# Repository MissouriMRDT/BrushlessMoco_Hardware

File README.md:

# Brushless Motor Controller R&D
The brushless moco is an electrical board that will simplify the electrical system within the brushless arm. This doesn't only include the brushless arm but also everything else that will use a significantly large brushless motors. This project provides future use cases for both **drivetrain** and **brushless arm** going forth.

[Main Project Document](https://mailmissouri.sharepoint.com/:w:/r/sites/SDELC-MarsRoverDesignTeam-Ogrp/_layouts/15/Doc.aspx?sourcedoc=%7BEC210861-7018-4F6B-87D7-A1866F1C1E35%7D&file=Brushless%20Motor%20Controller.docx&action=default&mobileredirect=true)

[Discord Forum](https://discord.com/channels/988649090306961418/1396668404471042090)

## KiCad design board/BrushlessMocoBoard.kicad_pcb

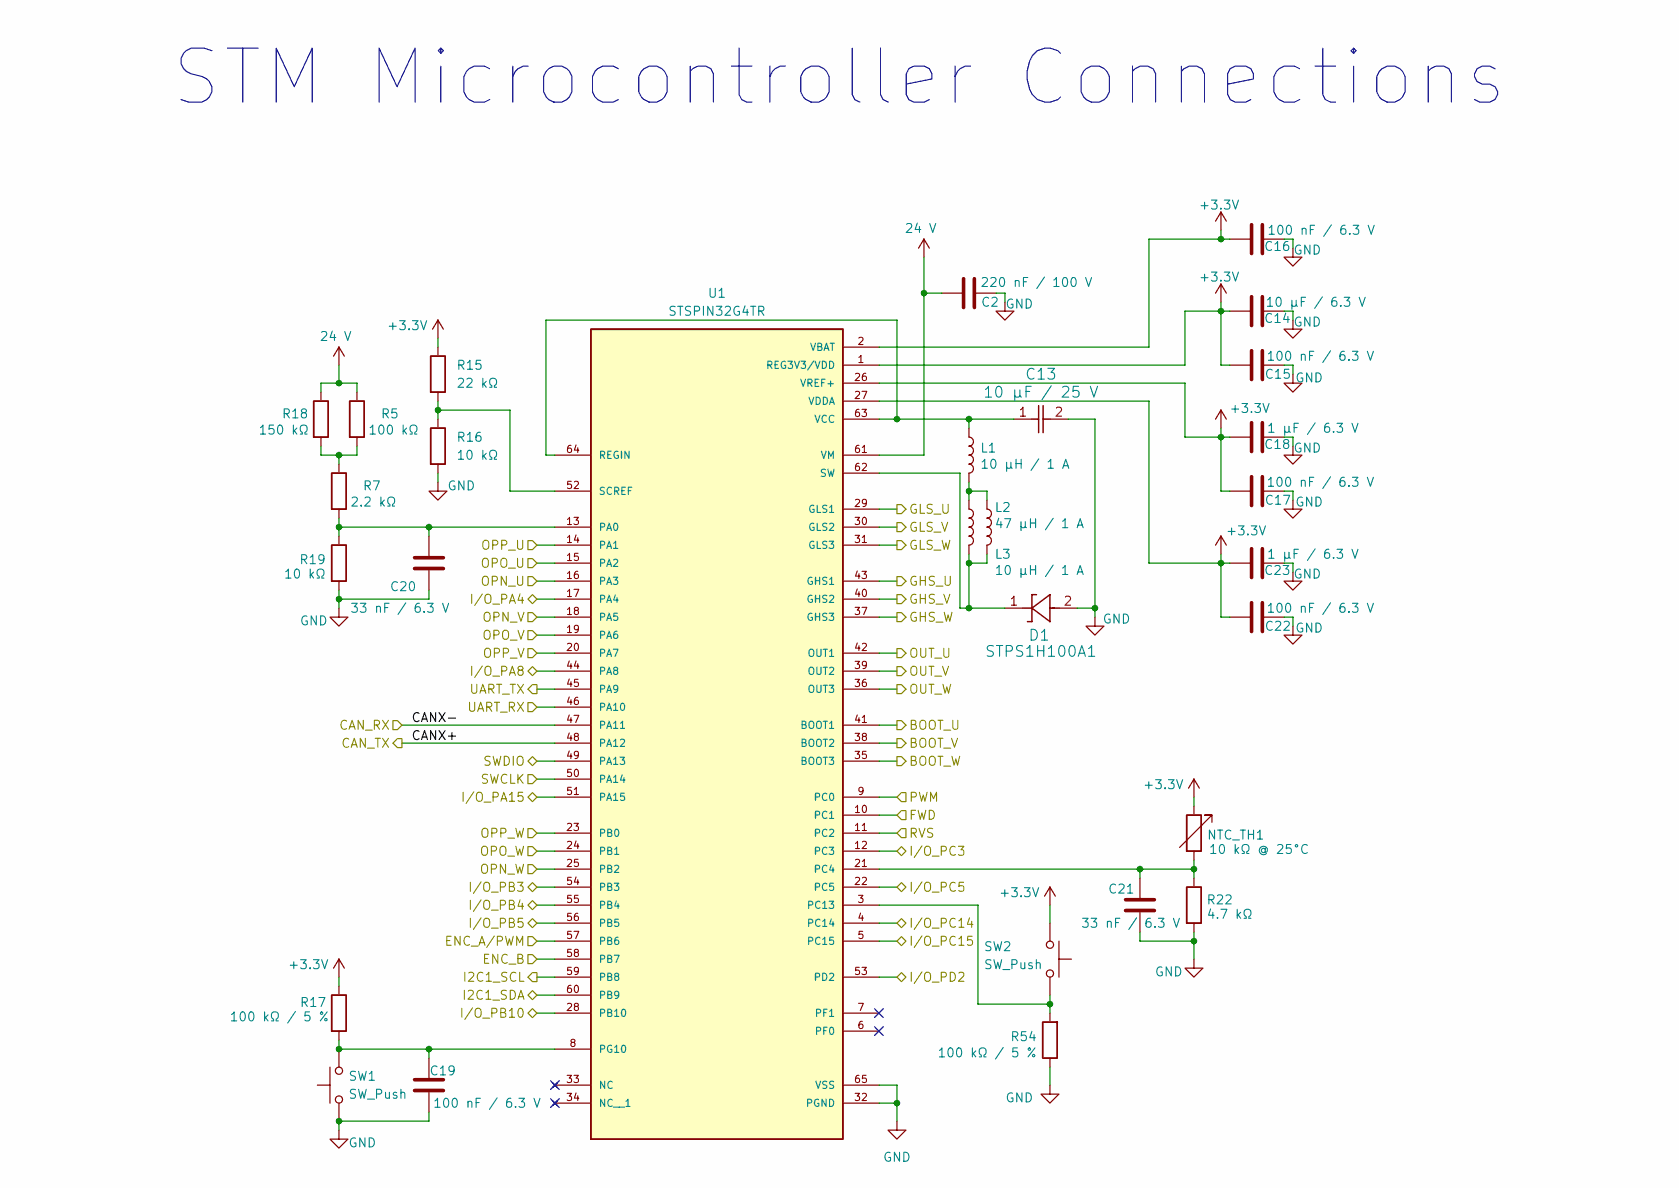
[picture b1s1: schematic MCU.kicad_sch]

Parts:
C2: 220 nF / 100 V; C_0603_1608Metric_Pad1.08x0.95mm_HandSolder
C13: 10 µF / 25 V; CAP_PAN_4X7_PAN
C14: 10 μF / 6.3 V; C_0603_1608Metric_Pad1.08x0.95mm_HandSolder
C15, C16, C17, C19, C22: 100 nF / 6.3 V; C_0603_1608Metric_Pad1.08x0.95mm_HandSolder
C18, C23: 1 μF / 6.3 V; C_0603_1608Metric_Pad1.08x0.95mm_HandSolder
C20, C21: 33 nF / 6.3 V; C_0603_1608Metric_Pad1.08x0.95mm_HandSolder
L1, L3: 10 μH / 1 A; L_1008_2520Metric_Pad1.43x2.20mm_HandSolder
L2: 47 μH / 1 A; IND_VLS5045EX-470M
NTC_TH1: 10 kΩ @ 25°C; R_0603_1608Metric_Pad0.98x0.95mm_HandSolder
R5: 100 kΩ; R_0603_1608Metric_Pad0.98x0.95mm_HandSolder
R7: 2.2 kΩ; R_0603_1608Metric_Pad0.98x0.95mm_HandSolder
R15: 22 kΩ; R_0603_1608Metric_Pad0.98x0.95mm_HandSolder
R16, R19: 10 kΩ; R_0603_1608Metric_Pad0.98x0.95mm_HandSolder
R17, R54: 100 kΩ / 5 %; R_0603_1608Metric_Pad0.98x0.95mm_HandSolder
R18: 150 kΩ; R_0603_1608Metric_Pad0.98x0.95mm_HandSolder
R22: 4.7 kΩ; R_0603_1608Metric_Pad0.98x0.95mm_HandSolder
STPS1H100A1: D1; SMA_STM
SW1, SW2: SW_Push; SW_SPST_TL3305A
U1: STSPIN32G4TR; QFN50P900X900X100-65N; PARTREV 2

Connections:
24 V: C2.1, R5.1, R18.1, U1.61 (VM); also elsewhere on the board
+3.3V: C14.1, C15.1, C16.1, C17.1, C18.1, C22.1, C23.1, NTC_TH1.1, R15.1, R17.1, SW2.1, U1.1 (REG3V3/VDD), U1.2 (VBAT), U1.26 (VREF+), U1.27 (VDDA); also elsewhere on the board
/Half-Bridges & Current Sensing/BOOT_U: U1.41 (BOOT1); also elsewhere on the board
/Half-Bridges & Current Sensing/BOOT_V: U1.38 (BOOT2); also elsewhere on the board
/Half-Bridges & Current Sensing/BOOT_W: U1.35 (BOOT3); also elsewhere on the board
/Half-Bridges & Current Sensing/GHS_U: U1.43 (GHS1); also elsewhere on the board
/Half-Bridges & Current Sensing/GHS_V: U1.40 (GHS2); also elsewhere on the board
/Half-Bridges & Current Sensing/GHS_W: U1.37 (GHS3); also elsewhere on the board
/Half-Bridges & Current Sensing/GLS_U: U1.29 (GLS1); also elsewhere on the board
/Half-Bridges & Current Sensing/GLS_V: U1.30 (GLS2); also elsewhere on the board
/Half-Bridges & Current Sensing/GLS_W: U1.31 (GLS3); also elsewhere on the board
/Half-Bridges & Current Sensing/OPN_U: U1.16 (PA3); also elsewhere on the board
/Half-Bridges & Current Sensing/OPN_V: U1.18 (PA5); also elsewhere on the board
/Half-Bridges & Current Sensing/OPN_W: U1.25 (PB2); also elsewhere on the board
/Half-Bridges & Current Sensing/OPO_U: U1.15 (PA2); also elsewhere on the board
/Half-Bridges & Current Sensing/OPO_V: U1.19 (PA6); also elsewhere on the board
/Half-Bridges & Current Sensing/OPO_W: U1.24 (PB1); also elsewhere on the board
/Half-Bridges & Current Sensing/OPP_U: U1.14 (PA1); also elsewhere on the board
/Half-Bridges & Current Sensing/OPP_V: U1.20 (PA7); also elsewhere on the board
/Half-Bridges & Current Sensing/OPP_W: U1.23 (PB0); also elsewhere on the board
/Half-Bridges & Current Sensing/OUT_U: U1.42 (OUT1); also elsewhere on the board
/Half-Bridges & Current Sensing/OUT_V: U1.39 (OUT2); also elsewhere on the board
/Half-Bridges & Current Sensing/OUT_W: U1.36 (OUT3); also elsewhere on the board
/Interfaces/ENC_A/PWM: U1.57 (PB6); also elsewhere on the board
/Interfaces/ENC_B: U1.58 (PB7); also elsewhere on the board
/Interfaces/FWD: U1.10 (PC1); also elsewhere on the board
/Interfaces/I2C1_SCL: U1.59 (PB8); also elsewhere on the board
/Interfaces/I2C1_SDA: U1.60 (PB9); also elsewhere on the board
/Interfaces/I/O_PA4: U1.17 (PA4); also elsewhere on the board
/Interfaces/I/O_PA8: U1.44 (PA8); also elsewhere on the board
/Interfaces/I/O_PA15: U1.51 (PA15); also elsewhere on the board
/Interfaces/I/O_PB3: U1.54 (PB3); also elsewhere on the board
/Interfaces/I/O_PB4: U1.55 (PB4); also elsewhere on the board
/Interfaces/I/O_PB5: U1.56 (PB5); also elsewhere on the board
/Interfaces/I/O_PB10: U1.28 (PB10); also elsewhere on the board
/Interfaces/I/O_PC3: U1.12 (PC3); also elsewhere on the board
/Interfaces/I/O_PC5: U1.22 (PC5); also elsewhere on the board
/Interfaces/I/O_PC14: U1.4 (PC14); also elsewhere on the board
/Interfaces/I/O_PC15: U1.5 (PC15); also elsewhere on the board
/Interfaces/I/O_PD2: U1.53 (PD2); also elsewhere on the board
/Interfaces/PWM: U1.9 (PC0); also elsewhere on the board
/Interfaces/RVS: U1.11 (PC2); also elsewhere on the board
/Interfaces/SWCLK: U1.50 (PA14); also elsewhere on the board
/Interfaces/SWDIO: U1.49 (PA13); also elsewhere on the board
/Interfaces/UART_RX: U1.46 (PA10); also elsewhere on the board
/Interfaces/UART_TX: U1.45 (PA9); also elsewhere on the board
/MCU/CANX+: U1.48 (PA12); also elsewhere on the board
/MCU/CANX-: U1.47 (PA11); also elsewhere on the board
GND: C2.2, C13.2, C14.2, C15.2, C16.2, C17.2, C18.2, C19.2, C20.2, C21.2, C22.2, C23.2, R16.2, R19.2, R22.2, R54.1, STPS1H100A1.2, SW1.1, U1.32 (PGND), U1.65 (VSS); also elsewhere on the board
unnamed: L1.2, L2.1, L3.1
unnamed: R5.2, R7.1, R18.2
unnamed: C20.1, R7.2, R19.1, U1.13 (PA0)
unnamed: C21.1, NTC_TH1.2, R22.1, U1.21 (PC4)
unnamed: R54.2, SW2.2, U1.3 (PC13)
unnamed: C19.1, R17.2, SW1.2, U1.8 (PG10)
unnamed: C13.1, L1.1, U1.63 (VCC), U1.64 (REGIN)
unnamed: R15.2, R16.1, U1.52 (SCREF)
unnamed: L2.2, L3.2, STPS1H100A1.1, U1.62 (SW)

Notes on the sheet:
STM Microcontroller Connections

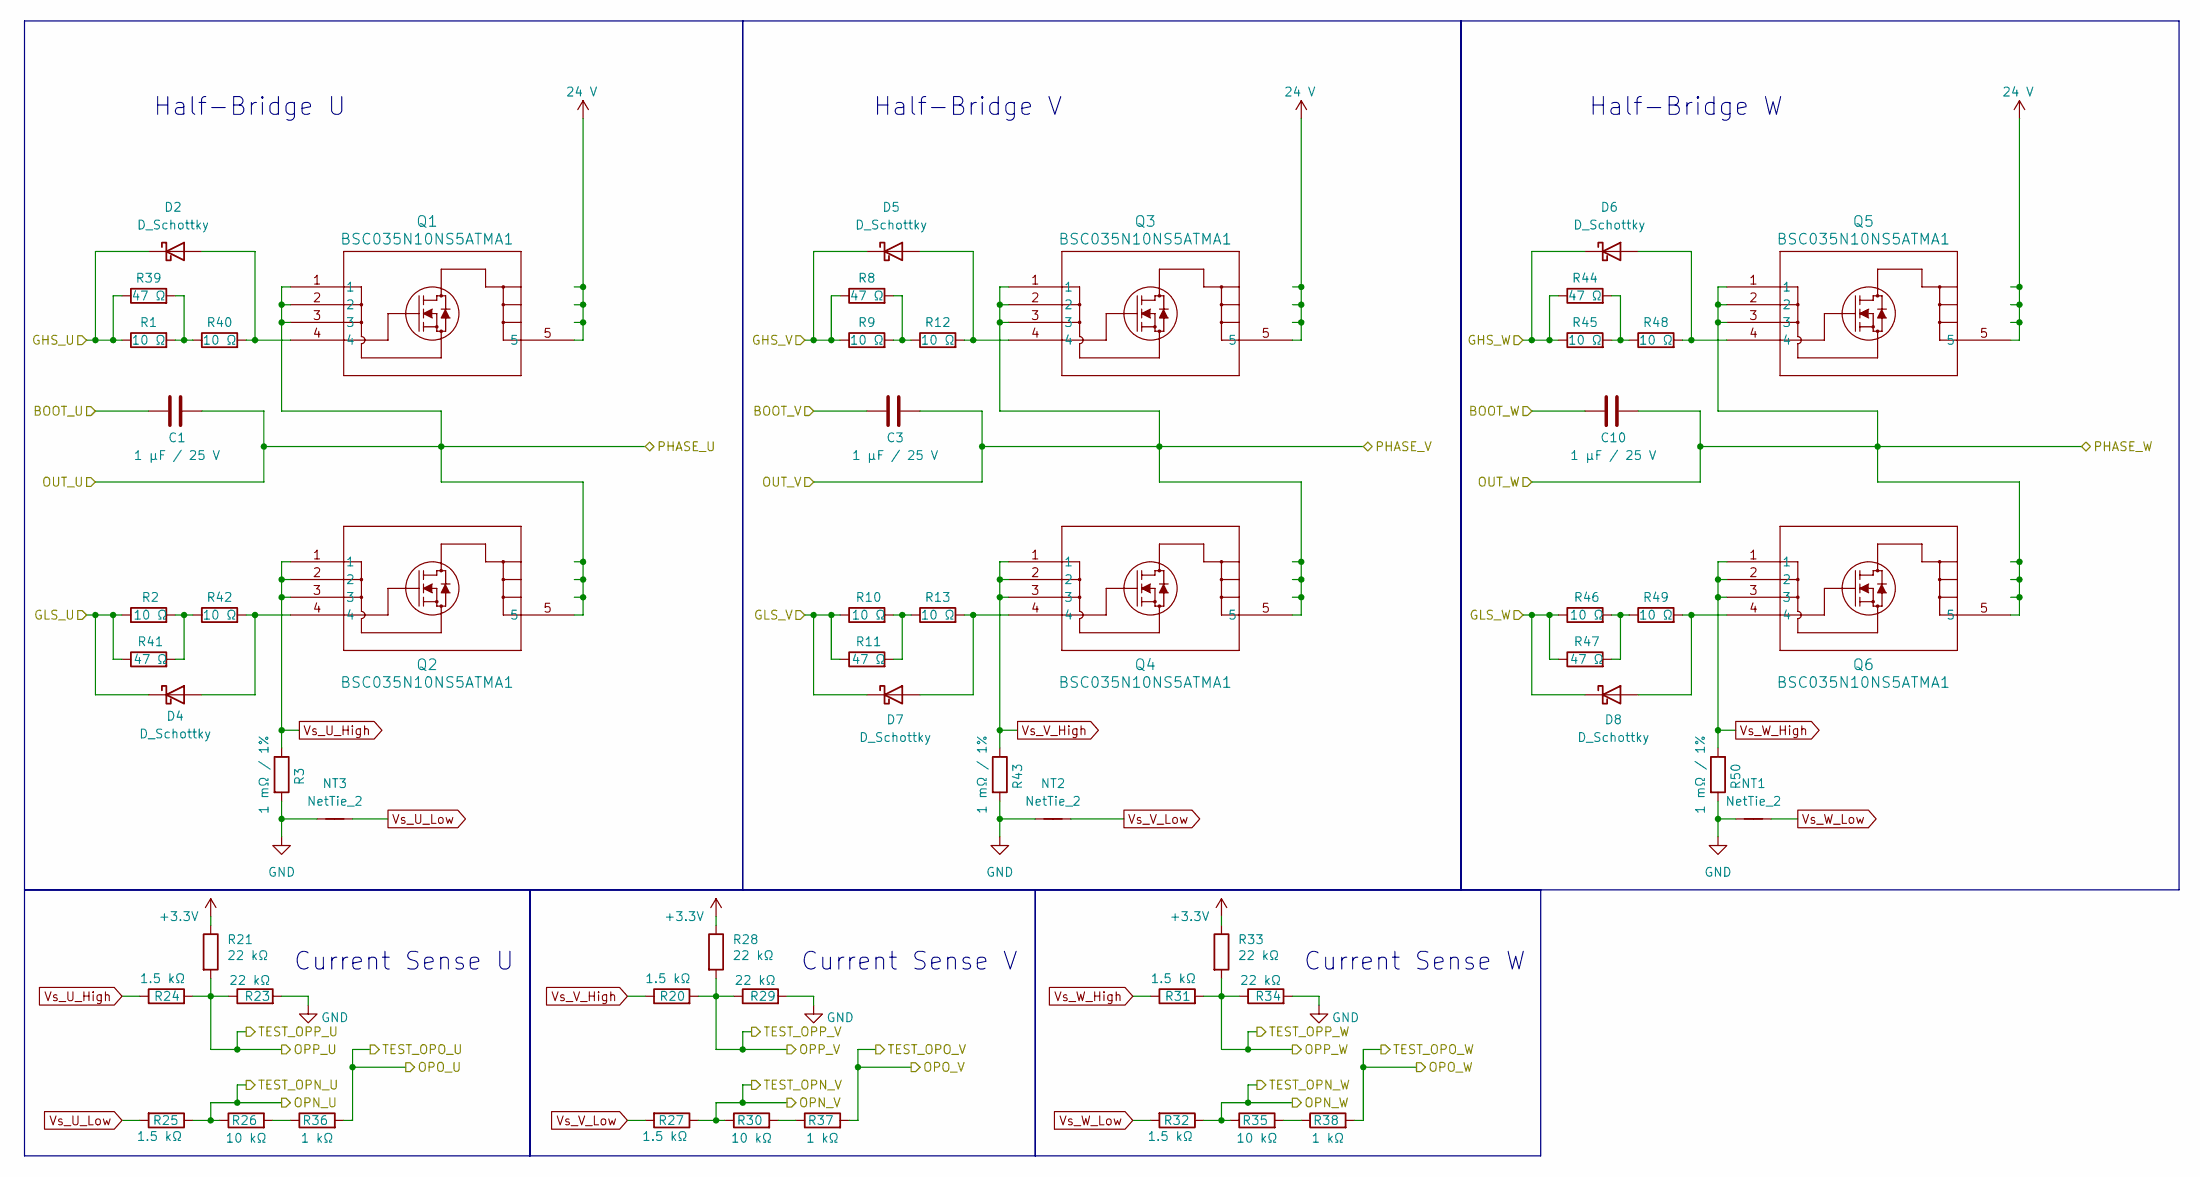
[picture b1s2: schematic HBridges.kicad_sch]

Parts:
C1, C3, C10: 1 µF / 25 V; C_0603_1608Metric_Pad1.08x0.95mm_HandSolder
D2, D4, D5, D6, D7, D8: D_Schottky; D_SOD-123
NT1, NT2, NT3: NetTie_2; NetTie-2_SMD_Pad0.5mm
Q1, Q2, Q3, Q4, Q5, Q6: BSC035N10NS5ATMA1; PG-TDSON-8_INF
R1, R2, R9, R10, R12, R13, R40, R42, R45, R46, R48, R49: 10 Ω; R_0603_1608Metric_Pad0.98x0.95mm_HandSolder
R3, R43, R50: 1 mΩ / 1%; R_1206_3216Metric_Pad1.30x1.75mm_HandSolder
R8, R11, R39, R41, R44, R47: 47 Ω; R_0603_1608Metric_Pad0.98x0.95mm_HandSolder
R20, R24, R25, R27, R31, R32: 1.5 kΩ; R_0603_1608Metric_Pad0.98x0.95mm_HandSolder
R21, R23, R28, R29, R33, R34: 22 kΩ; R_0603_1608Metric_Pad0.98x0.95mm_HandSolder
R26, R30, R35: 10 kΩ; R_0603_1608Metric_Pad0.98x0.95mm_HandSolder
R36, R37, R38: 1 kΩ; R_0603_1608Metric_Pad0.98x0.95mm_HandSolder

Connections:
24 V: Q1.5, Q3.5, Q5.5; also elsewhere on the board
+3.3V: R21.1, R28.1, R33.1; also elsewhere on the board
/Half-Bridges & Current Sensing/BOOT_U: C1.1; also elsewhere on the board
/Half-Bridges & Current Sensing/BOOT_V: C3.1; also elsewhere on the board
/Half-Bridges & Current Sensing/BOOT_W: C10.1; also elsewhere on the board
/Half-Bridges & Current Sensing/GHS_U: D2.1 (K), R1.1, R39.1; also elsewhere on the board
/Half-Bridges & Current Sensing/GHS_V: D5.1 (K), R8.1, R9.1; also elsewhere on the board
/Half-Bridges & Current Sensing/GHS_W: D6.1 (K), R44.1, R45.1; also elsewhere on the board
/Half-Bridges & Current Sensing/GLS_U: D4.1 (K), R2.1, R41.1; also elsewhere on the board
/Half-Bridges & Current Sensing/GLS_V: D7.1 (K), R10.1, R11.1; also elsewhere on the board
/Half-Bridges & Current Sensing/GLS_W: D8.1 (K), R46.1, R47.1; also elsewhere on the board
/Half-Bridges & Current Sensing/OPN_U: R25.1, R26.1; also elsewhere on the board
/Half-Bridges & Current Sensing/OPN_V: R27.1, R30.1; also elsewhere on the board
/Half-Bridges & Current Sensing/OPN_W: R32.1, R35.1; also elsewhere on the board
/Half-Bridges & Current Sensing/OPO_U: R36.2; also elsewhere on the board
/Half-Bridges & Current Sensing/OPO_V: R37.2; also elsewhere on the board
/Half-Bridges & Current Sensing/OPO_W: R38.2; also elsewhere on the board
/Half-Bridges & Current Sensing/OPP_U: R21.2, R23.1, R24.2; also elsewhere on the board
/Half-Bridges & Current Sensing/OPP_V: R20.2, R28.2, R29.1; also elsewhere on the board
/Half-Bridges & Current Sensing/OPP_W: R31.2, R33.2, R34.1; also elsewhere on the board
/Half-Bridges & Current Sensing/OUT_U: C1.2, Q1.1, Q1.2, Q1.3, Q2.5; also elsewhere on the board
/Half-Bridges & Current Sensing/OUT_V: C3.2, Q3.1, Q3.2, Q3.3, Q4.5; also elsewhere on the board
/Half-Bridges & Current Sensing/OUT_W: C10.2, Q5.1, Q5.2, Q5.3, Q6.5; also elsewhere on the board
GND: NT1.1, NT2.1, NT3.1, R3.2, R23.2, R29.2, R34.2, R43.2, R50.2; also elsewhere on the board
unnamed: D2.2 (A), Q1.4, R40.2
unnamed: D4.2 (A), Q2.4, R42.2
unnamed: D5.2 (A), Q3.4, R12.2
unnamed: D6.2 (A), Q5.4, R48.2
unnamed: D7.2 (A), Q4.4, R13.2
unnamed: D8.2 (A), Q6.4, R49.2
unnamed: R1.2, R39.2, R40.1
unnamed: R2.2, R41.2, R42.1
unnamed: R10.2, R11.2, R13.1
unnamed: R8.2, R9.2, R12.1
unnamed: R26.2, R36.1
unnamed: R30.2, R37.1
unnamed: R35.2, R38.1
unnamed: R44.2, R45.2, R48.1
unnamed: R46.2, R47.2, R49.1
Vs_U_High: Q2.1, Q2.2, Q2.3, R3.1, R24.1
Vs_U_Low: NT3.2, R25.2
Vs_V_High: Q4.1, Q4.2, Q4.3, R20.1, R43.1
Vs_V_Low: NT2.2, R27.2
Vs_W_High: Q6.1, Q6.2, Q6.3, R31.1, R50.1
Vs_W_Low: NT1.2, R32.2

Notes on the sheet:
Current Sense V
Half-Bridge U
Current Sense W
Half-Bridge V
Half-Bridge W
Current Sense U

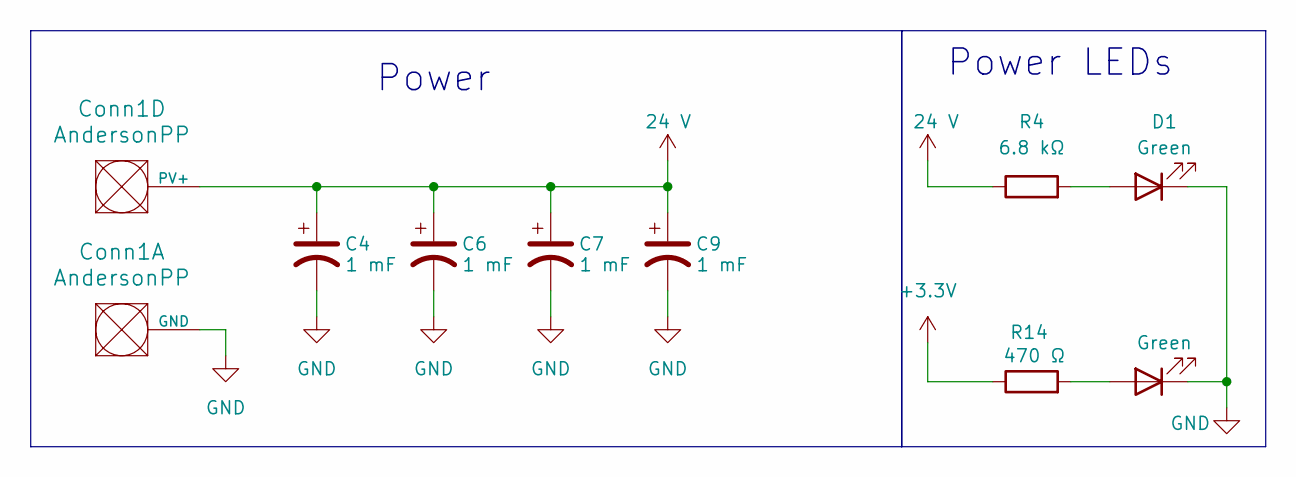
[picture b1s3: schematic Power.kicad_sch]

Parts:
C4, C6, C7, C9: 1 mF; CP_Radial_D16.0mm_P7.50mm
Conn1: AndersonPP; Square_Anderson_2_H_Side_By_Side_PV
D1, D3: Green; LED_0603_1608Metric_Pad1.05x0.95mm_HandSolder
R4: 6.8 kΩ; R_0603_1608Metric_Pad0.98x0.95mm_HandSolder
R14: 470 Ω; R_0603_1608Metric_Pad0.98x0.95mm_HandSolder

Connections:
24 V: C4.1, C6.1, C7.1, C9.1, Conn1.4 (PV+), R4.1; also elsewhere on the board
+3.3V: R14.1; also elsewhere on the board
GND: C4.2, C6.2, C7.2, C9.2, Conn1.1 (GND), D1.1 (K), D3.1 (K); also elsewhere on the board
unnamed: D1.2 (A), R4.2
unnamed: D3.2 (A), R14.2

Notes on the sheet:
Power LEDs
Power

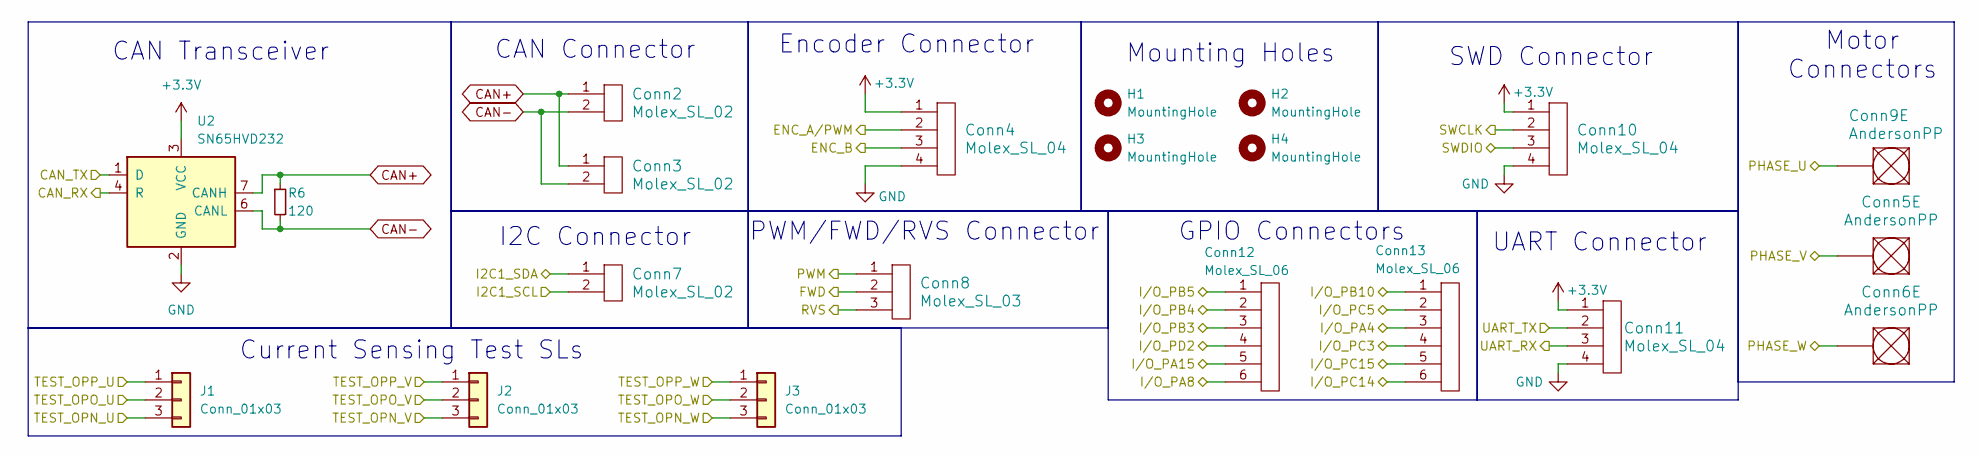
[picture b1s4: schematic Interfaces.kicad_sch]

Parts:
Conn2, Conn3, Conn7: Molex_SL_02; MOLEX_SL_02_Vertical
Conn4, Conn10, Conn11: Molex_SL_04; MOLEX_SL_04_Vertical
Conn5, Conn6, Conn9: AndersonPP; Square_Anderson_1_H
Conn8: Molex_SL_03; MOLEX_SL_03_Vertical
Conn12, Conn13: Molex_SL_06; MOLEX_SL_06_Vertical
H1, H2, H3, H4: MountingHole; 4_40_Hole
J1, J2, J3: Conn_01x03; PinSocket_1x03_P2.54mm_Vertical
R6: 120; R_0603_1608Metric_Pad0.98x0.95mm_HandSolder
U2: SN65HVD232; SOIC-8_3.9x4.9mm_P1.27mm

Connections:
+3.3V: Conn4.1, Conn10.1, Conn11.1, U2.3 (VCC); also elsewhere on the board
/Half-Bridges & Current Sensing/OPN_U: J1.3; also elsewhere on the board
/Half-Bridges & Current Sensing/OPN_V: J2.3; also elsewhere on the board
/Half-Bridges & Current Sensing/OPN_W: J3.3; also elsewhere on the board
/Half-Bridges & Current Sensing/OPO_U: J1.2; also elsewhere on the board
/Half-Bridges & Current Sensing/OPO_V: J2.2; also elsewhere on the board
/Half-Bridges & Current Sensing/OPO_W: J3.2; also elsewhere on the board
/Half-Bridges & Current Sensing/OPP_U: J1.1; also elsewhere on the board
/Half-Bridges & Current Sensing/OPP_V: J2.1; also elsewhere on the board
/Half-Bridges & Current Sensing/OPP_W: J3.1; also elsewhere on the board
/Half-Bridges & Current Sensing/OUT_U: Conn9.1 (GND); also elsewhere on the board
/Half-Bridges & Current Sensing/OUT_V: Conn5.1 (GND); also elsewhere on the board
/Half-Bridges & Current Sensing/OUT_W: Conn6.1 (GND); also elsewhere on the board
/Interfaces/ENC_A/PWM: Conn4.2; also elsewhere on the board
/Interfaces/ENC_B: Conn4.3; also elsewhere on the board
/Interfaces/FWD: Conn8.2; also elsewhere on the board
/Interfaces/I2C1_SCL: Conn7.2; also elsewhere on the board
/Interfaces/I2C1_SDA: Conn7.1; also elsewhere on the board
/Interfaces/I/O_PA4: Conn13.3; also elsewhere on the board
/Interfaces/I/O_PA8: Conn12.6; also elsewhere on the board
/Interfaces/I/O_PA15: Conn12.5; also elsewhere on the board
/Interfaces/I/O_PB3: Conn12.3; also elsewhere on the board
/Interfaces/I/O_PB4: Conn12.2; also elsewhere on the board
/Interfaces/I/O_PB5: Conn12.1; also elsewhere on the board
/Interfaces/I/O_PB10: Conn13.1; also elsewhere on the board
/Interfaces/I/O_PC3: Conn13.4; also elsewhere on the board
/Interfaces/I/O_PC5: Conn13.2; also elsewhere on the board
/Interfaces/I/O_PC14: Conn13.6; also elsewhere on the board
/Interfaces/I/O_PC15: Conn13.5; also elsewhere on the board
/Interfaces/I/O_PD2: Conn12.4; also elsewhere on the board
/Interfaces/PWM: Conn8.1; also elsewhere on the board
/Interfaces/RVS: Conn8.3; also elsewhere on the board
/Interfaces/SWCLK: Conn10.2; also elsewhere on the board
/Interfaces/SWDIO: Conn10.3; also elsewhere on the board
/Interfaces/UART_RX: Conn11.3; also elsewhere on the board
/Interfaces/UART_TX: Conn11.2; also elsewhere on the board
/MCU/CANX+: U2.1 (D); also elsewhere on the board
/MCU/CANX-: U2.4 (R); also elsewhere on the board
CAN+: Conn2.1, Conn3.1, R6.1, U2.7 (CANH)
CAN-: Conn2.2, Conn3.2, R6.2, U2.6 (CANL)
GND: Conn4.4, Conn10.4, Conn11.4, U2.2 (GND); also elsewhere on the board

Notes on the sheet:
CAN Transceiver
Encoder Connector
PWM/FWD/RVS Connector
I2C Connector
GPIO Connectors
CAN Connector
Mounting Holes
Current Sensing Test SLs
UART Connector
SWD Connector
Motor Connectors

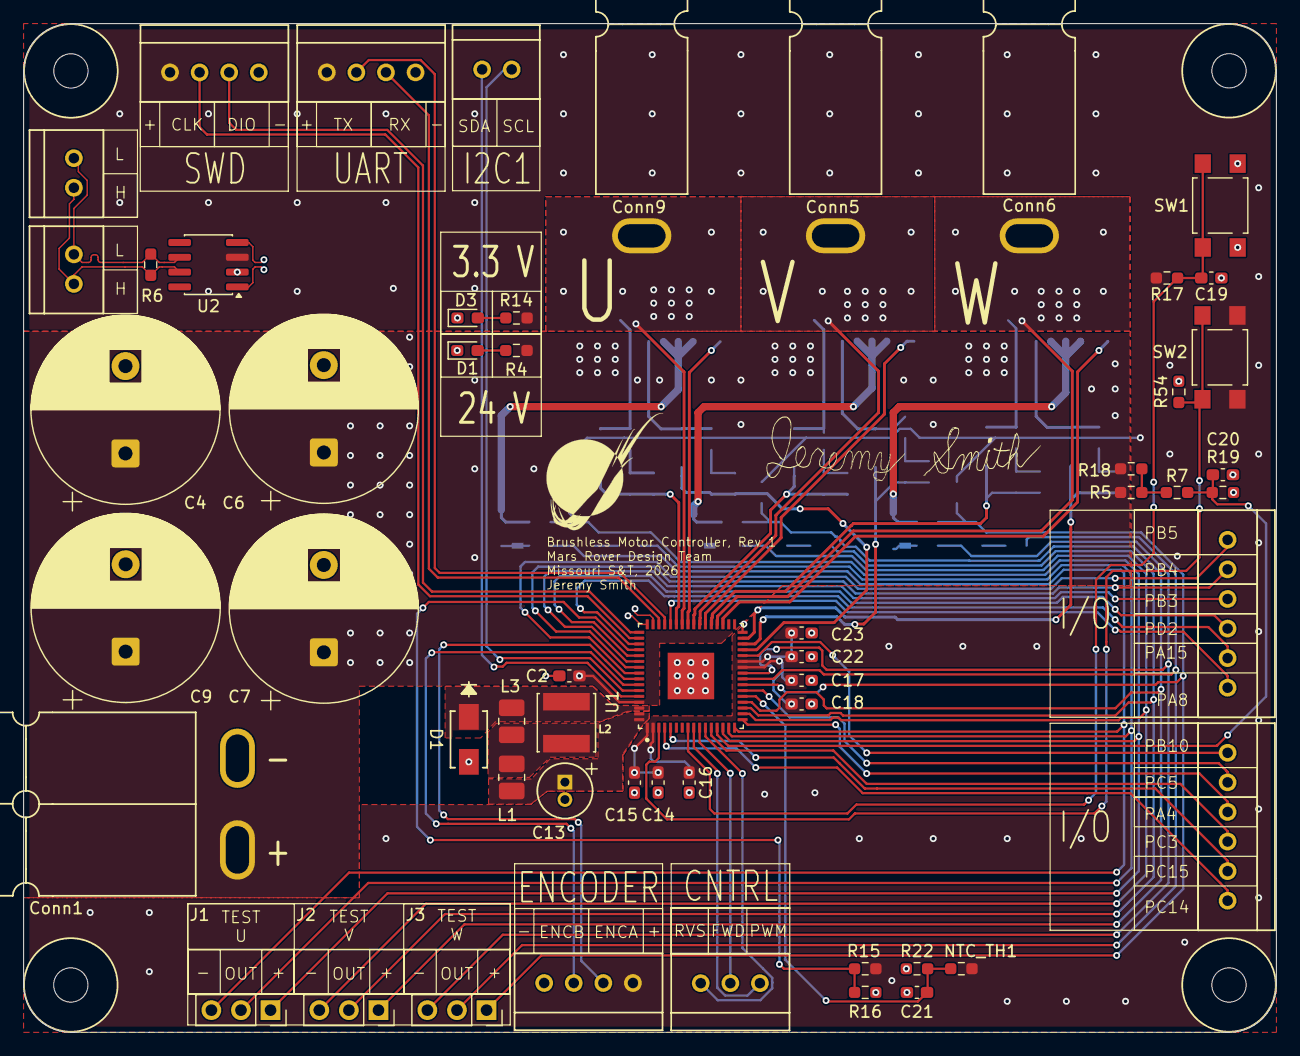
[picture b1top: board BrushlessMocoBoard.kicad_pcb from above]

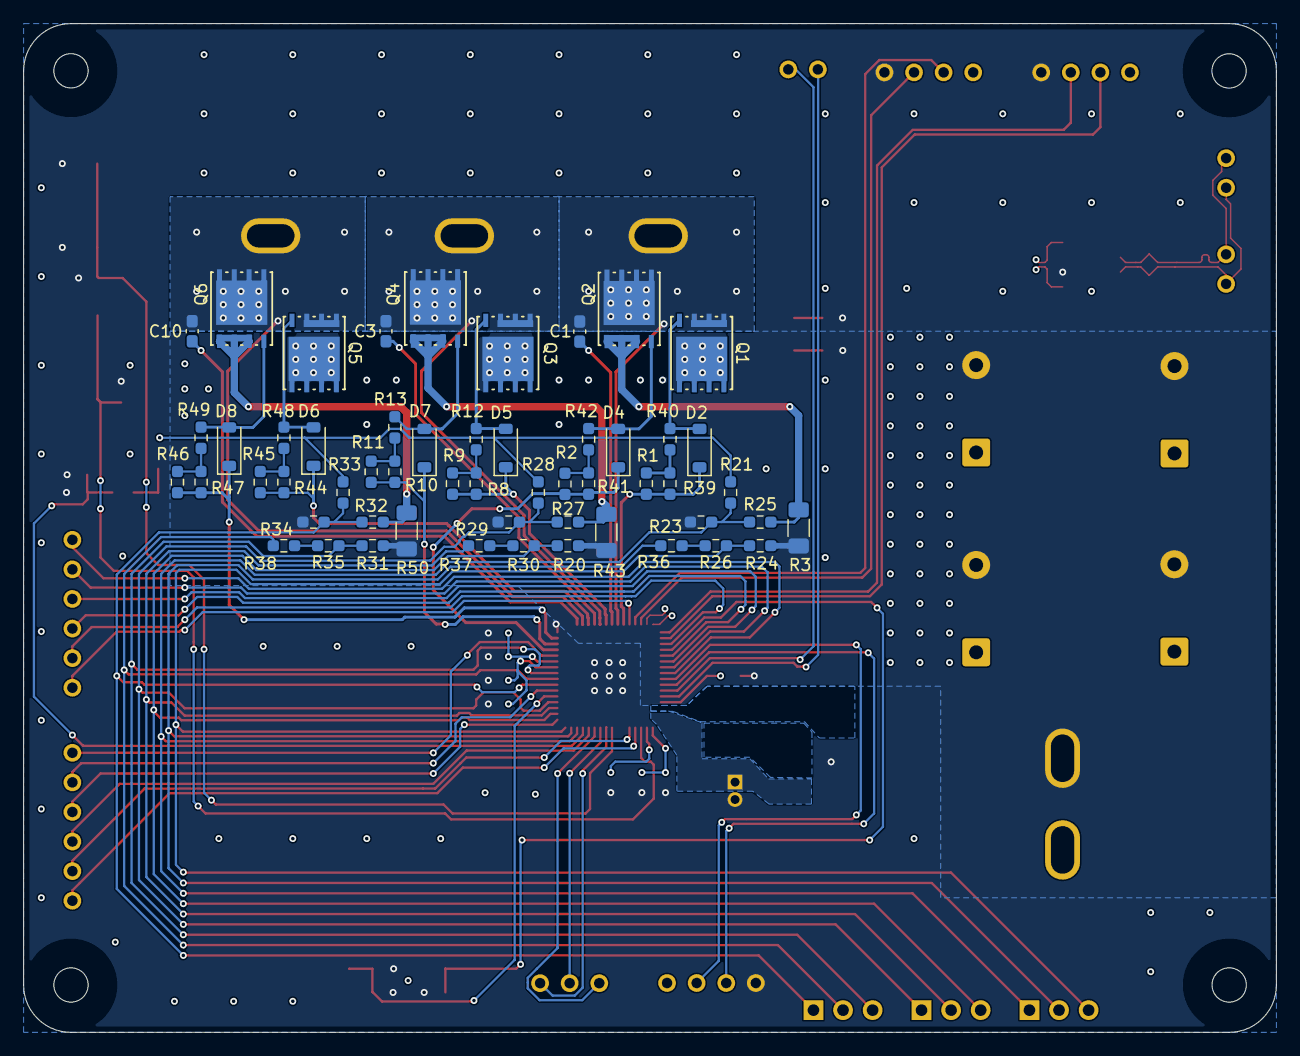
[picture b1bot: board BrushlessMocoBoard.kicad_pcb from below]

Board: 4 copper layers, 107.6 x 86.6 mm, 116 parts (57 on the bottom side), 83 nets.

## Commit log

2025-03-03 Added some stuff. Testing that commit is workings
2025-03-03 Test to see if the board properly commits
2025-03-03 Testing Header coloring in readme files
2025-03-03 testing still
2025-03-03 test
2025-03-03 Tests didn't work here is most recent readme
2025-03-05 Added some stuff to the hard ware. Mostly where to put circuits on the schematic
2025-06-21 Setup
2025-06-21 Started inverter design
2025-06-22 Switched fets
2025-06-22 Added can transciever and current sensor symbols and libraries
2025-09-08 Added kicad workflow
2025-09-08 Added project name to github action
2025-10-02 Began work on the schematic w/ CAN and buck application circuits.
2025-10-06 Swapped buck to OKI
2025-10-09 Added MCU and initial half bridge circuits from application circuit.
2025-10-16 Added connections around the MCU from the application circuit from the data sheet, VCC, VDD, VREF+, etc.
2025-10-23 Completed basic application circuit from MCU datasheet and adjusted Hierarchical Paths.
2025-10-29 Added CAN and Encoder connectors.
2025-10-30 Added some resistor and capacitor values.
2025-10-31 Added resistor values to current sense circuit.
2025-11-07 Finished adding component values to circuits, except for 4 filtering capacitors
2025-11-13 Implemented some fixes discussed during the board review.
2025-11-20 Fixed many issues brought up in the schematic review.
2025-11-21 Fixed everything mentioned in schematic review, should be ready for second review/layout.
2025-12-05 Updated footprints for schematic
2026-01-22 Adjusted schematic footprints
2026-01-28 Adjusted diode footprints and grouped layout components
2026-02-05 Placed some basic planes in the layout and swapped mosfet symbols to match layout footprints.
2026-02-05 Regrouped components on the layout into a rough draft before the next set of zoning and tracing.
2026-02-11 Significant progress on board layout. Added GPIO and UART pins, also rearranged encoder and I2C MCU pins.
2026-02-12 Rearranged components on the layout, added a switch, and connected hierarchical labels in the schematic.
2026-02-19 Updated footprints to fix issues found in board review.
2026-02-20 Made layout adjustments according to board review.
2026-02-26 Fixed footprint and symbol for FETs
2026-02-27 First draft of wiring for the layout finished.
2026-03-06 Tentatively finished rev1.
2026-03-07 Fixed text on the board.
2026-03-16 Fixed many issues found in Rev1 review prior to order
2026-03-17 Added Cvm to schematic, need to add to layout as well
2026-03-20 Added footprints to board library
2026-03-23 Final board as ordered
2026-04-15 Fixed i/o pin silkscreen labels
